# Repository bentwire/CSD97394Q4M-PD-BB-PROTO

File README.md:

# CSD97394Q4M-PD-BB-PROTO
Crazy idea using 2 CSD97394Q4M and an inductor to make a bidirectional buck-boost supply for USB PD

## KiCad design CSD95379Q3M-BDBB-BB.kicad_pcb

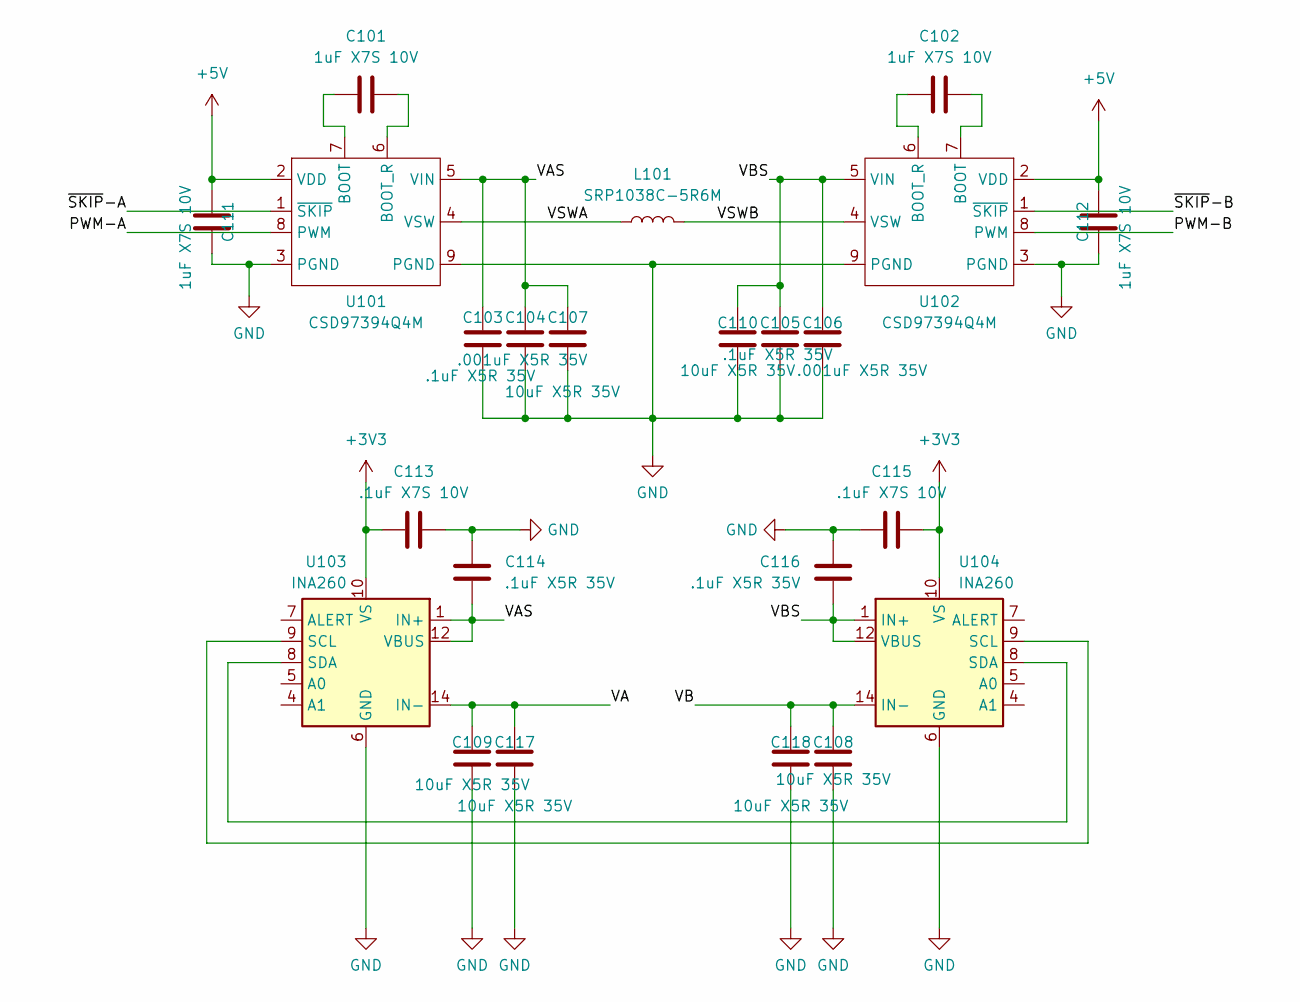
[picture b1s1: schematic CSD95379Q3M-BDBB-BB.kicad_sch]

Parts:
C101, C102, C111, C112: 1uF X7S 10V; C_0402_1005Metric
C103, C105, C114, C116: .1uF X5R 35V; C_0402_1005Metric
C104, C106: .001uF X5R 35V; C_0402_1005Metric
C107, C108, C109, C110, C117, C118: 10uF X5R 35V; C_0805_2012Metric
C113, C115: .1uF X7S 10V; C_0402_1005Metric
L101: SRP1038C-5R6M; L_Bourns_SRP1038C_10.0x10.0mm
U101, U102: CSD97394Q4M; 8-PowerVFDFN-VSON-CLIP
U103, U104: INA260; TSSOP-16_4.4x5mm_P0.65mm

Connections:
+3V3: C113.2, C115.2, U103.10 (VS), U104.10 (VS)
+5V: C111.2, C112.2, U101.2 (VDD), U102.2 (VDD)
/PWM-A: U101.8 (PWM)
/PWM-B: U102.8 (PWM)
/VA: C109.2, C117.2, U103.14 (IN-), U103.15 (IN-), U103.16 (IN-)
/VAS: C103.2, C104.2, C107.2, C114.2, U101.5 (VIN), U103.1 (IN+), U103.2 (IN+), U103.3 (IN+), U103.12 (VBUS)
/VB: C108.2, C118.2, U104.14 (IN-), U104.15 (IN-), U104.16 (IN-)
/VBS: C105.2, C106.2, C110.2, C116.2, U102.5 (VIN), U104.1 (IN+), U104.2 (IN+), U104.3 (IN+), U104.12 (VBUS)
/VSWA: L101.1, U101.4 (VSW)
/VSWB: L101.2, U102.4 (VSW)
/~SKIP-A: U101.1 (~SKIP)
/~SKIP-B: U102.1 (~SKIP)
GND: C103.1, C104.1, C105.1, C106.1, C107.1, C108.1, C109.1, C110.1, C111.1, C112.1, C113.1, C114.1, C115.1, C116.1, C117.1, C118.1, U101.3 (PGND), U101.9 (PGND), U102.3 (PGND), U102.9 (PGND), U103.6 (GND), U103.11 (GND), U104.6 (GND), U104.11 (GND)
unnamed: C101.1, U101.7 (BOOT)
unnamed: C101.2, U101.6 (BOOT_R)
unnamed: C102.2, U102.7 (BOOT)
unnamed: C102.1, U102.6 (BOOT_R)
unnamed: U103.9 (SCL), U104.9 (SCL)
unnamed: U103.8 (SDA), U104.8 (SDA)

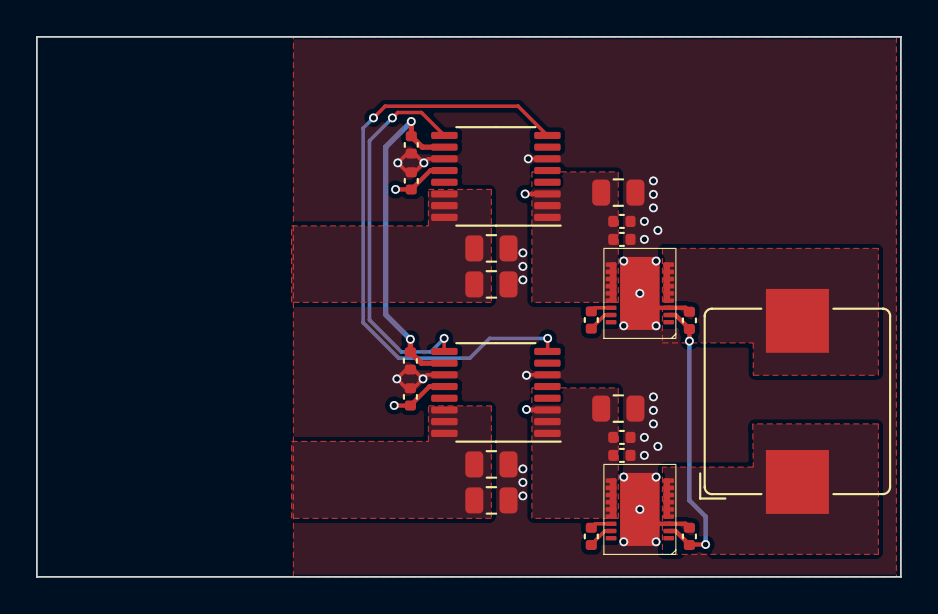
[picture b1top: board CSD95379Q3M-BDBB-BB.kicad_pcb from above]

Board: 4 copper layers, 48.0 x 30.0 mm, 23 parts (0 on the bottom side), 15 nets.

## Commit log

2023-10-13 Route some more stuff, move things a bit.
2023-10-13 Fixed a net name.
